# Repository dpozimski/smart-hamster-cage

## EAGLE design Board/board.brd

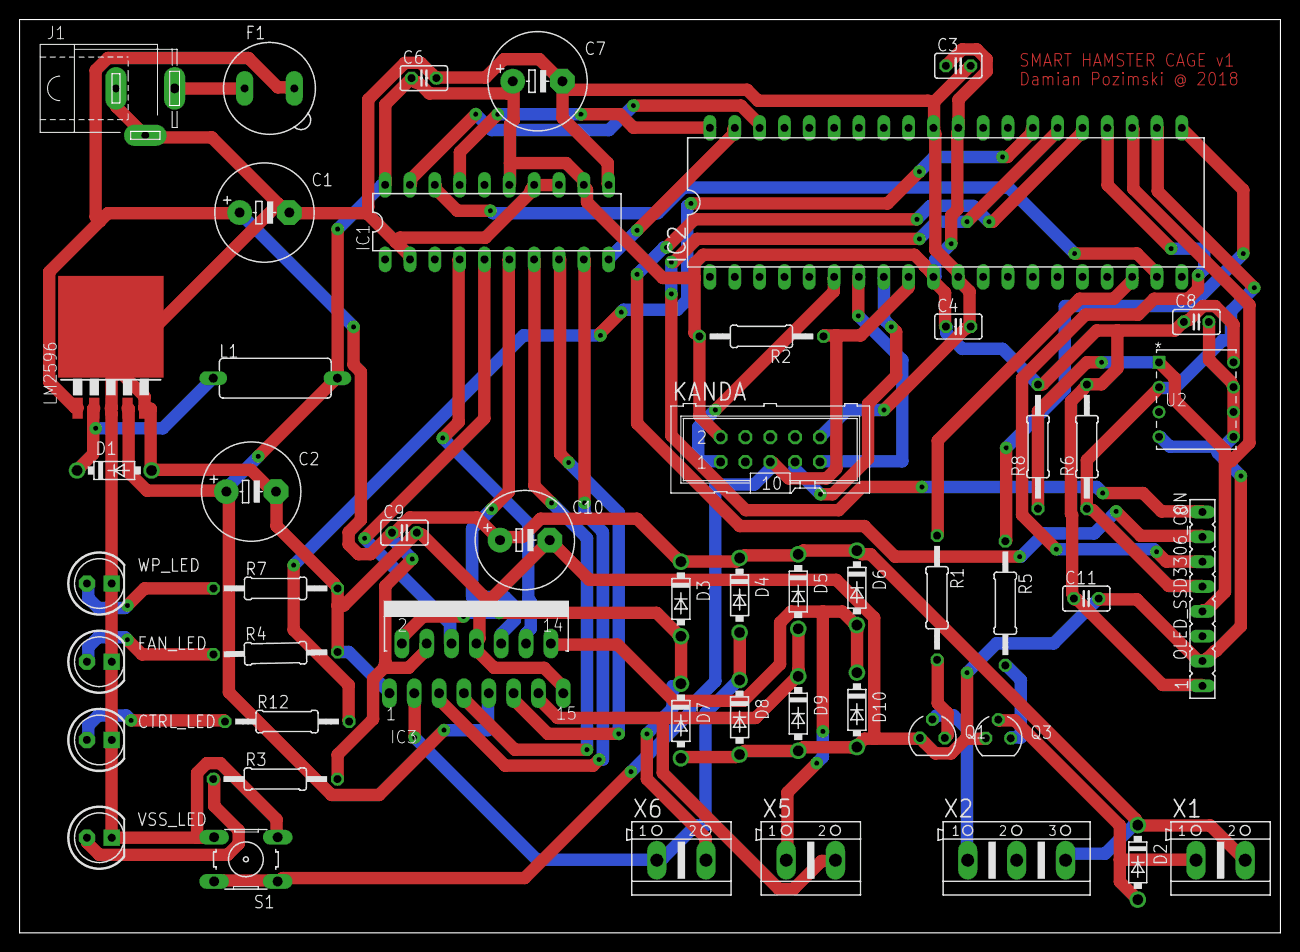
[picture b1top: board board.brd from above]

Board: 2 copper layers, 129.0 x 93.4 mm, 50 parts (0 on the bottom side), 39 nets.

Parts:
C1: 470uF; E5-10,5
C2: 220uF; E5-10,5
C3, C4, C6, C8, C9, C11: 100nF; C025-025X050
C7: 10uF; E5-10,5
C10: 22uF; E5-10,5
CTRL_LED: LED5MM
D1, D2, D3, D4, D5, D6, D7, D8, D9, D10: 1N5822; DO41-7.6
F1: 250V/2A 135°C; 19560
FAN_LED: LED5MM
IC1: L297; DIL20
IC2: MEGA32-P; DIL40
IC3: L298; MULTIWATT-15
J1: +12V; SPC4078
KANDA: ML10
L1: 33uH; BC12
LM2596: TO263-5
OLED_SSD3306_CON: FE08
Q1, Q3: BC639; SOT54D
R1, R5: 240R; 0207/12
R2: 10K; 0207/12
R3, R4, R7: 470R; 0207/12
R6, R8: 4K7; 0207/12
R12: 330R; 0207/12
S1: B3F-10XX
U2: DS1621+; 21-0043D_8
VSS_LED: LED5MM
WP_LED: LED5MM
X1: WATER_PUMP; AK500/2
X2: FAN; AK500/3
X5: SM_CD; AK500/2
X6: SM_AB; AK500/2

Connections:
GND: C1.-, C2.-, C3.2, C4.2, C6.2, C7.-, C8.2, C9.2, C10.-, C11.2, CTRL_LED.K, D1.A, D7.A, D8.A, D9.A, D10.A, FAN_LED.K, IC1.2, IC1.11, IC1.13, IC1.14, IC2.11, IC2.31, IC3.1, IC3.8, IC3.15, J1.1, J1.2, KANDA.10, LM2596.3, LM2596.5, LM2596.6, OLED_SSD3306_CON.2, Q1.E, Q3.E, R4.2, R7.2, S1.3, S1.4, U2.4, U2.5, U2.6, U2.7, VSS_LED.K, WP_LED.K
unnamed: F1.1, J1.3
unnamed: D1.C, L1.1, LM2596.2
unnamed: IC2.6, KANDA.1
unnamed: IC2.8, KANDA.7
unnamed: IC2.7, KANDA.9
unnamed: R3.1, VSS_LED.A
unnamed: Q1.B, R1.2
unnamed: Q1.C, X2.1
unnamed: IC2.9, KANDA.5, R2.1, S1.1, S1.2
unnamed: IC2.27, R12.2
unnamed: IC2.21, R5.1
unnamed: IC1.9, IC3.5
unnamed: CTRL_LED.A, R12.1
unnamed: IC1.5, IC3.6
unnamed: IC1.4, IC3.12
unnamed: IC1.17, IC2.40
unnamed: IC1.18, IC2.19
unnamed: IC1.10, IC2.39
unnamed: IC1.19, IC2.38
unnamed: IC1.8, IC3.11
unnamed: R7.1, WP_LED.A
unnamed: FAN_LED.A, R4.1
unnamed: D6.A, D10.C, IC3.14, X5.1
unnamed: D3.A, D7.C, IC3.2, X6.2
unnamed: D4.A, D8.C, IC3.3, X6.1
unnamed: D5.A, D9.C, IC3.13, X5.2
unnamed: Q3.B, R5.2
unnamed: D2.A, Q3.C, X1.1
unnamed: IC2.18, R1.1
unnamed: IC2.23, OLED_SSD3306_CON.4, R8.1, U2.1
unnamed: IC2.22, OLED_SSD3306_CON.5, R6.1, U2.2
unnamed: IC2.24, OLED_SSD3306_CON.6
unnamed: IC2.25, OLED_SSD3306_CON.7
unnamed: IC2.26, OLED_SSD3306_CON.8
unnamed: IC1.7, IC3.7
unnamed: IC1.6, IC3.10
VCC: C2.+, C3.1, C4.1, C6.1, C7.+, C8.1, C11.1, IC1.12, IC1.15, IC1.20, IC2.10, IC2.30, IC3.9, KANDA.2, L1.2, LM2596.4, OLED_SSD3306_CON.1, R2.2, R6.2, R8.2, U2.8
VSS: C1.+, C9.1, C10.+, D2.C, D3.C, D4.C, D5.C, D6.C, F1.2, IC3.4, LM2596.1, R3.2, X1.2, X2.3

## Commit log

2018-03-30 Initial source project
2018-03-30 Add avrdude as tool
2018-03-30 Do not include Debug and Release output files
2018-03-30 uC test
2018-03-31 Power supply
2018-04-02 MCU + Kanda input
2018-04-07 Fan, water pump, and supply for motor drive eagle
2018-04-07 L297 to uC
2018-04-07 Signal leds to connectors
2018-04-07 mcp9808
2018-04-08 stepper motor l298
2018-04-08 added filter for vss l298
2018-04-09 Added pcb design #1
2018-04-09 auto route
2018-04-09 added 5mm vss led
2018-04-09 gnd line
2018-04-09 rc 1.0
2018-04-10 Added I2C device class
2018-04-10 endWrite
2018-04-15 PWM devices code
2018-04-15 Device as an abstract device
2018-04-15 steppermotor device
2018-04-15 ControlLed device
2018-04-15 init
2018-04-15 OLED_Screen layer
2018-04-17 wip i2c
2018-04-18 Temperature module support
2018-04-18 oled display layer
2018-04-18 clear && flus
2018-04-18 flow & uicontroller
2018-04-18 flow classes
2018-04-19 Controller base class to define a basic behavior for refreshing logic modules
2018-04-19 Timr0 as counter, Timer1 output b for fan
2018-04-20 controller base type
2018-04-20 Added new inductor
2018-04-20 Resistor value
2018-04-20 init process
2018-04-20 First Release Candidate - logic completed STATUS: waiting for tests
2018-04-21 SCL/SDA thermometer
2018-04-21 Rename 1N5824 - 1N5822
2018-04-21 pptx
2018-04-21 deleted unused file
2018-04-22 AREF cannot be connected to VCC
2018-04-27 10mil for corners
2018-04-29 Drill 0.5
2018-04-29 DRC rule for 0.5mm drill
2018-04-29 Diameter 1.3
2018-04-29 PWM devices checked
2018-04-29 Timer as normal input device
2018-04-29 UiController values
2018-04-29 OutputTimeRules mechanism
2018-04-29 Add i2c lib from github && i2c bus work for thermometer
2018-05-15 OLED
2018-05-27 i2c mine implmentation im mk oled lib
2018-06-15 max pwm water pouring to 20
2018-06-15 Change range value
2018-06-16 PWM/time values changed for presentation
2018-06-24 Zipped scheme
2018-07-02 Added comments to the header files
